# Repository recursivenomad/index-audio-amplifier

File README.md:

🎧 **Tiny USB-C audio amplifier for off-ear BMR speakers**
===========================================================

&nbsp;

> &nbsp;
> ### ***Work in progress***
> &nbsp;

&nbsp;

***Features***
==============

*Coming soon...*

&nbsp;

***How to use***
================

*Coming soon...*

&nbsp;

***License / Access***
======================

This original work is freely available under your choice of the [*MIT-0*](./LICENSE.txt) license or [*CC0-1.0*][URL-CC0] public domain dedication.  
Although attribution is not required, sharing when you've made something with my work is really cool 💖

----------------------

*Repository: <https://gitlab.com/recursivenomad/index-audio-amplifier/>*  
*Contact: <recursivenomad@protonmail.com>*

----------------------

[URL-MIT-0]: <https://opensource.org/license/mit-0/>
[URL-CC0]: <https://creativecommons.org/publicdomain/zero/1.0/>

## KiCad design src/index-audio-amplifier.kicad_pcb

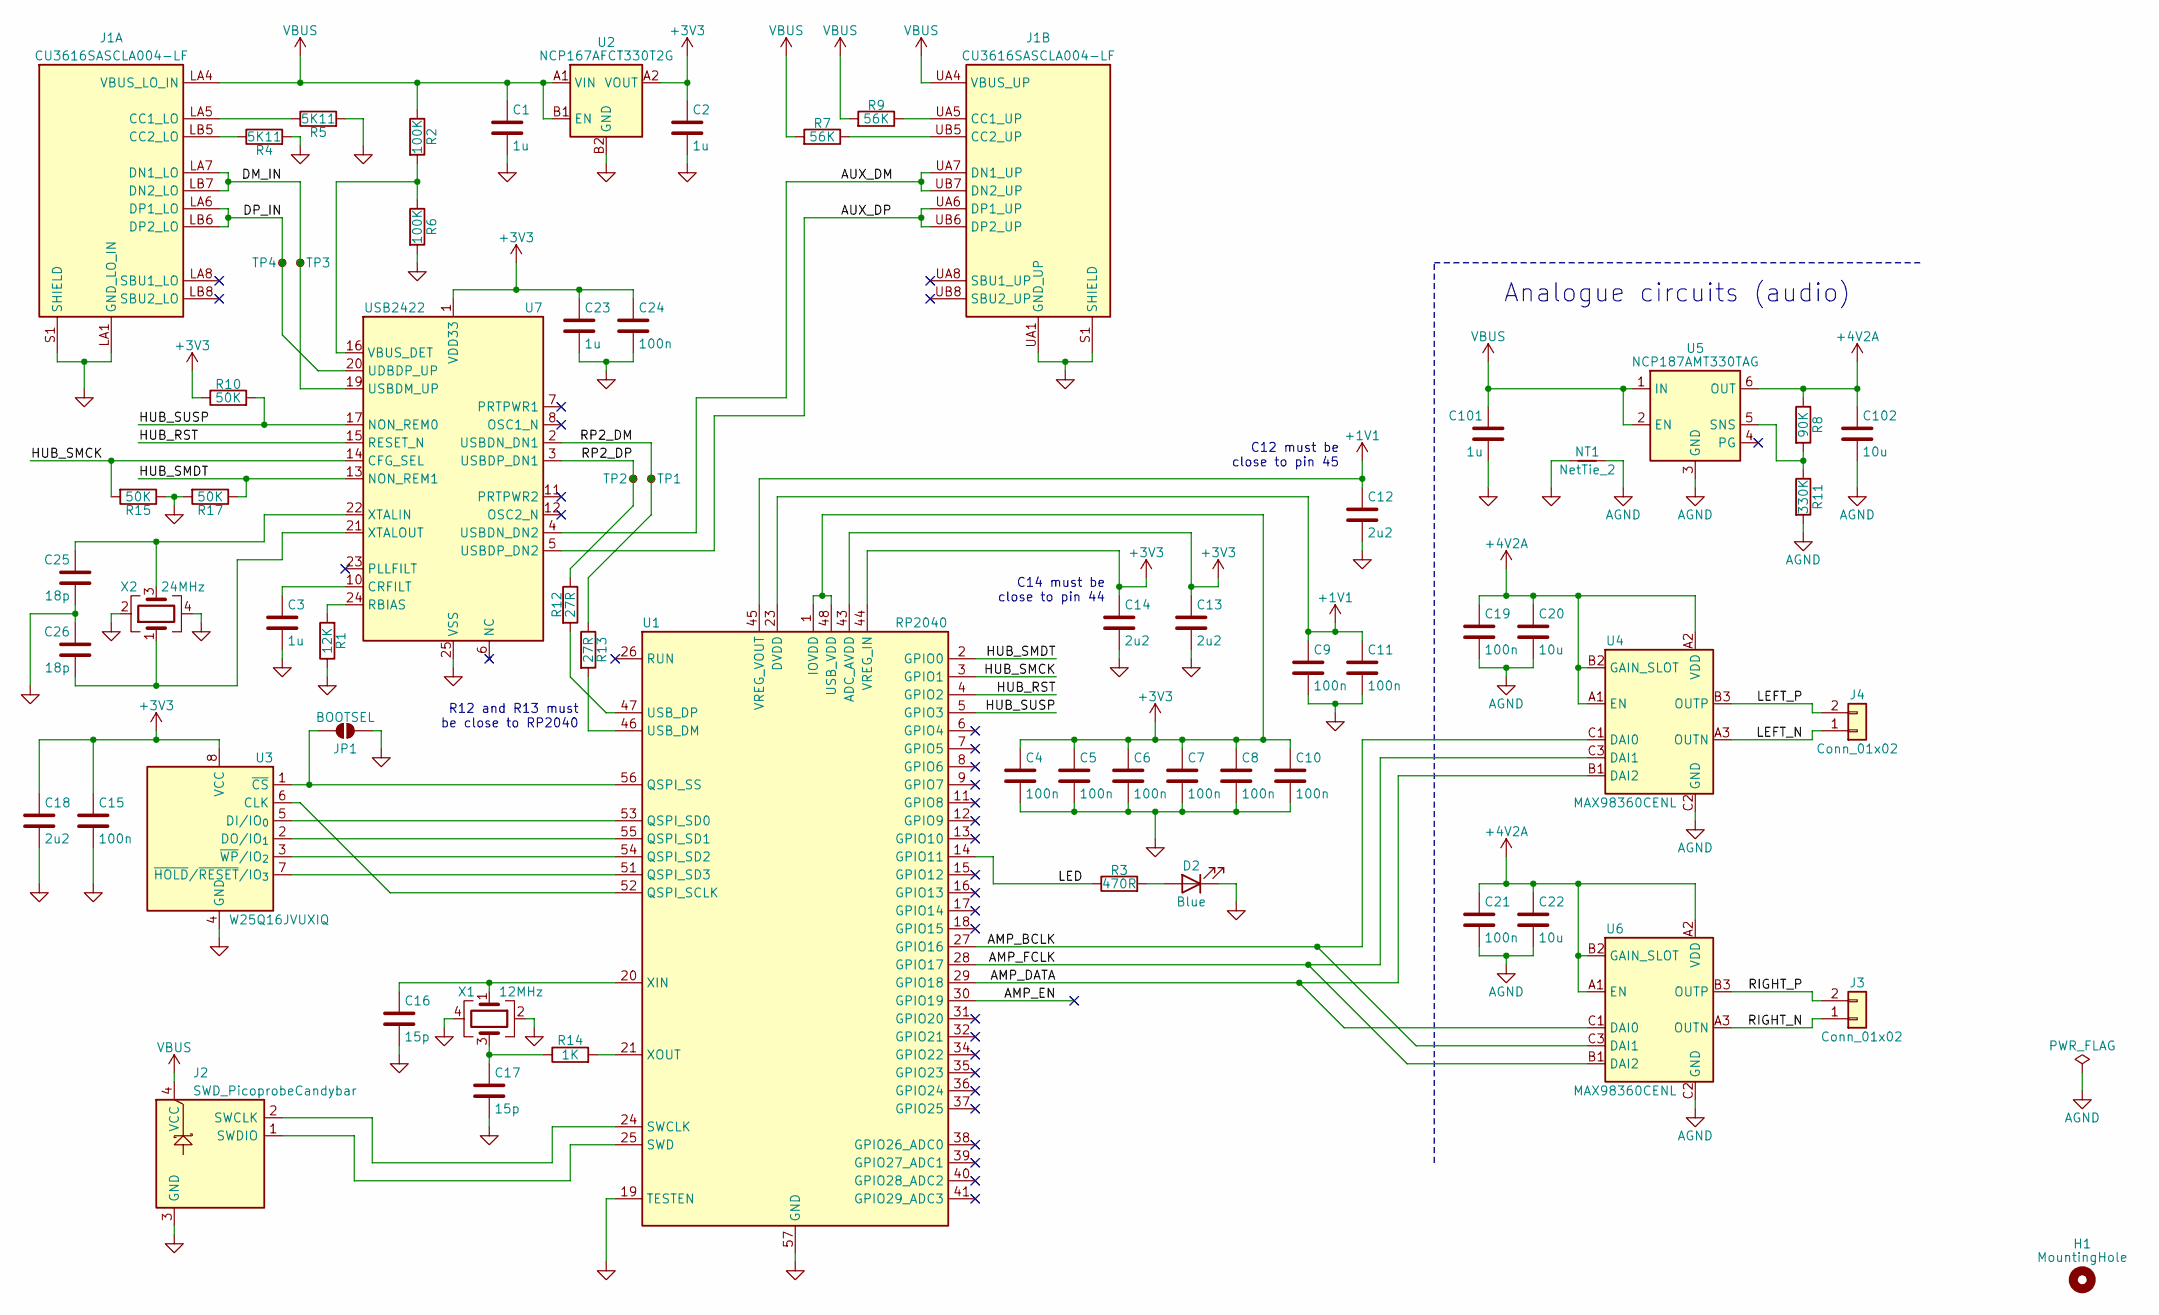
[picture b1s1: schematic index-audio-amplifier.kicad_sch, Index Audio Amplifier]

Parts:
C1, C2, C3, C23, C101: 1u; C_0402_1005Metric
C4, C5, C6, C7, C8, C9, C10, C11, C15, C19, C21, C24: 100n; C_0402_1005Metric
C12, C13, C14: 2u2; C_01005_0402Metric
C16, C17: 15p; C_0402_1005Metric
C18: 2u2; C_0402_1005Metric
C20, C22, C102: 10u; C_0402_1005Metric
C25, C26: 18p; C_0402_1005Metric
D2: Blue; LED_0603_1608Metric
H1: MountingHole; MountingHole_2.2mm_M2_ISO7380
J1: CU3616SASCLA004-LF; USB_C_Receptacle_CviLux_CU36SASCLA004-LF
J2: SWD_PicoprobeCandybar; SWD_PicoprobeCandybar_PressFit_Compact
J3, J4: Conn_01x02; PinHeader_1x02_P1.00mm_Vertical
JP1: BOOTSEL; SolderJumper-2_P1.0mm_Open_RoundedPad0.5x1.0mm
NT1: NetTie_2; NetTie-2_SMD_Pad0.5mm
R1: 12K; R_0402_1005Metric
R2, R6: 100K; R_0402_1005Metric
R3: 470R; R_0402_1005Metric
R4, R5: 5K11; R_0402_1005Metric
R7, R9: 56K; R_0402_1005Metric
R8: 90K; R_0402_1005Metric
R10, R15, R17: 50K; R_0402_1005Metric
R11: 330K; R_0402_1005Metric
R12, R13: 27R; R_0402_1005Metric
R14: 1K; R_0402_1005Metric
TP1, TP2, TP3, TP4: TestPoint_Small; TestPoint_Pad_D0.5mm
U1: RP2040; QFN-56-1EP_7x7mm_P0.4mm_EP3.2x3.2mm
U2: NCP167AFCT330T2G; WLCSP-4_0.64x0.64mm_Layout2x2_P0.35mm
U3: W25Q16JVUXIQ; Winbond_USON-8-1EP_3x2mm_P0.5mm_EP0.2x1.6mm
U4, U6: MAX98360CENL; WLP-9_1.347x1.347mm_Layout3x3_P0.4mm
U5: NCP187AMT330TAG; DFN-6-1EP_2x2mm_P0.65mm_EP1.01x1.7mm
U7: USB2422; VQFN-24-1EP_4x4mm_P0.5mm_EP2.5x2.5mm_ThermalVias
X1: 12MHz; Crystal_SMD_3225-4Pin_3.2x2.5mm
X2: 24MHz; Crystal_SMD_3225-4Pin_3.2x2.5mm

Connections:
+1V1: C9.1, C11.1, C12.1, U1.23 (DVDD), U1.45 (VREG_VOUT), U1.50 (DVDD)
+3V3: C2.1, C4.1, C5.1, C6.1, C7.1, C8.1, C10.1, C13.1, C14.1, C15.1, C18.1, C23.1, C24.1, R10.1, U1.1 (IOVDD), U1.10 (IOVDD), U1.22 (IOVDD), U1.33 (IOVDD), U1.42 (IOVDD), U1.43 (ADC_AVDD), U1.44 (VREG_IN), U1.48 (USB_VDD), U1.49 (IOVDD), U2.A2 (VOUT), U3.8 (VCC), U7.1 (VDD33), U7.9 (VDD33), U7.18 (VDD33)
+4V2A: C19.1, C20.1, C21.1, C22.1, C102.1, R8.1, U4.A1 (EN), U4.A2 (VDD), U4.B2 (GAIN_SLOT), U5.6 (OUT), U6.A1 (EN), U6.A2 (VDD), U6.B2 (GAIN_SLOT)
/AMP_BCLK: U1.27 (GPIO16), U4.C1 (DAI0), U6.C3 (DAI1)
/AMP_DATA: U1.29 (GPIO18), U4.B1 (DAI2), U6.C1 (DAI0)
/AMP_EN: U1.30 (GPIO19)
/AMP_FCLK: U1.28 (GPIO17), U4.C3 (DAI1), U6.B1 (DAI2)
/AUX_DM: J1.UA7 (DN1_UP), J1.UB7 (DN2_UP), U7.4 (USBDN_DN2)
/AUX_DP: J1.UA6 (DP1_UP), J1.UB6 (DP2_UP), U7.5 (USBDP_DN2)
/DM_IN: J1.LA7 (DN1_LO), J1.LB7 (DN2_LO), TP3.1, U7.19 (USBDM_UP)
/DP_IN: J1.LA6 (DP1_LO), J1.LB6 (DP2_LO), TP4.1, U7.20 (UDBDP_UP)
/HUB_RST: U1.4 (GPIO2), U7.15 (RESET_N)
/HUB_SMCK: R15.2, U1.3 (GPIO1), U7.14 (CFG_SEL)
/HUB_SMDT: R17.1, U1.2 (GPIO0), U7.13 (NON_REM1)
/HUB_SUSP: R10.2, U1.5 (GPIO3), U7.17 (NON_REM0)
/LED: R3.1, U1.14 (GPIO11)
/LEFT_N: J4.1, U4.A3 (OUTN)
/LEFT_P: J4.2, U4.B3 (OUTP)
/RIGHT_N: J3.1, U6.A3 (OUTN)
/RIGHT_P: J3.2, U6.B3 (OUTP)
/RP2_DM: R13.1, TP1.1, U7.2 (USBDN_DN1)
/RP2_DP: R12.1, TP2.1, U7.3 (USBDP_DN1)
AGND: C19.2, C20.2, C21.2, C22.2, C102.2, NT1.2, R11.2, U4.C2 (GND), U5.3 (GND), U5.7 (GND), U6.C2 (GND)
GND: C1.2, C2.2, C3.2, C4.2, C5.2, C6.2, C7.2, C8.2, C9.2, C10.2, C11.2, C12.2, C13.2, C14.2, C15.2, C16.2, C17.2, C18.2, C23.2, C24.2, C25.2, C26.1, C101.2, D2.1 (K), J1.LA1 (GND_LO_IN), J1.LA12 (GND_LO), J1.LB1 (GND_LO), J1.LB12 (GND_LO), J1.S1 (SHIELD), J1.UA1 (GND_UP), J1.UA12 (GND_UP), J1.UB1 (GND_UP), J1.UB12 (GND_UP), J2.3 (GND), JP1.2 (B), NT1.1, R1.1, R4.2, R5.2, R6.2, R15.1, R17.2, U1.19 (TESTEN), U1.57 (GND), U2.B2 (GND), U3.4 (GND), U7.25 (VSS), X1.2, X1.4, X2.2, X2.4
unnamed: C17.1, R14.1, X1.3
unnamed: D2.2 (A), R3.2
unnamed: J1.LA5 (CC1_LO), R5.1
unnamed: J1.LB5 (CC2_LO), R4.1
unnamed: J1.UA5 (CC1_UP), R9.1
unnamed: J1.UB5 (CC2_UP), R7.1
unnamed: J2.2 (SWCLK), U1.24 (SWCLK)
unnamed: J2.1 (SWDIO), U1.25 (SWD)
unnamed: JP1.1 (A), U1.56 (QSPI_SS), U3.1 (~CS)
unnamed: U1.52 (QSPI_SCLK), U3.6 (CLK)
unnamed: U1.53 (QSPI_SD0), U3.5 (DI/IO_{0})
unnamed: U1.55 (QSPI_SD1), U3.2 (DO/IO_{1})
unnamed: U1.54 (QSPI_SD2), U3.3 (~WP/IO_{2})
unnamed: U1.51 (QSPI_SD3), U3.7 (~HOLD/~RESET/IO_{3})
unnamed: R13.2, U1.46 (USB_DM)
unnamed: R12.2, U1.47 (USB_DP)
unnamed: C16.1, U1.20 (XIN), X1.1
unnamed: R14.2, U1.21 (XOUT)
unnamed: R8.2, R11.1, U5.5 (SNS)
unnamed: C3.1, U7.10 (CRFILT)
unnamed: R1.2, U7.24 (RBIAS)
unnamed: R2.2, R6.1, U7.16 (VBUS_DET)
unnamed: C25.1, U7.22 (XTALIN), X2.3
unnamed: C26.2, U7.21 (XTALOUT), X2.1
VBUS: C1.1, C101.1, J1.LA4 (VBUS_LO_IN), J1.LA9 (VBUS_LO), J1.LB4 (VBUS_LO), J1.LB9 (VBUS_LO), J1.UA4 (VBUS_UP), J1.UA9 (VBUS_UP), J1.UB4 (VBUS_UP), J1.UB9 (VBUS_UP), J2.4 (VCC), R2.1, R7.2, R9.2, U2.A1 (VIN), U2.B1 (EN), U5.1 (IN), U5.2 (EN)

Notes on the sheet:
C14 must be close to pin 44
R12 and R13 must be close to RP2040
C12 must be close to pin 45
Analogue circuits (audio)

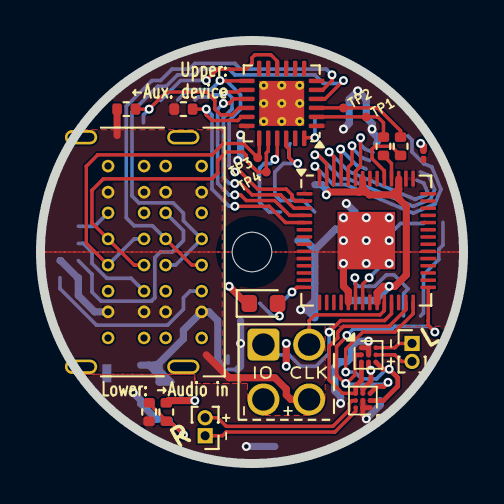
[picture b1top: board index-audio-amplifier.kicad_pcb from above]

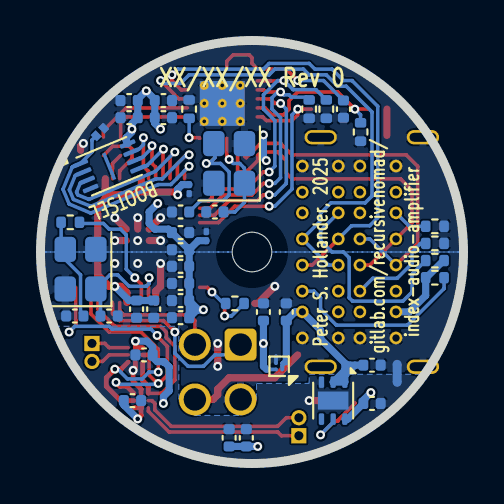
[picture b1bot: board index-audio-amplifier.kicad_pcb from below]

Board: 2 copper layers, 23.5 x 23.5 mm, 65 parts (45 on the bottom side), 48 nets.

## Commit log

2025-08-12 Initialize project
    KiCad 9.0.3
2025-08-12 Initialize project files
    KiCad 9.0.3
2025-08-12 Add & associate `compact-title-block` submodule
2025-08-12 Add & associate debug interface library
2025-08-13 Draw targeted in-situ reference for board layout
    Geometry approximated from Valve Index HMD using calipers
2025-08-13 Create board edge, 0.5mm clearance from nominal
2025-08-13 Recreate Pico schematic (ignoring connectors)
    <https://datasheets.raspberrypi.com/pico/pico-datasheet.pdf#pico-schematic-diagram>
2025-08-13 Add discrete component proximity notes
    Notes adopted from `RP2040_minimal_r2.kicad_pro` in "Minimal-KiCAD.zip"
    from "Hardware design with RP2040":
    <https://datasheets.raspberrypi.com/rp2040/hardware-design-with-rp2040.pdf#minimal-design-example>
2025-08-13 Add PCM5101A for `usb_sound_card` firmware
    Component selection adopted from `pico_vga_sd_aud.pro` in
    "VGA_KiCAD.zip" from "Hardware design with RP2040":
    <https://datasheets.raspberrypi.com/rp2040/hardware-design-with-rp2040.pdf#_the_vga_sd_card_audio_demo_boards_for_raspberry_pi_pico_and_raspberry_pi_pico_w>
    Referenced firmware is on the branch `usb-sound-card` in the
    index-audio-interface repository:
    <https://gitlab.com/recursivenomad/index-audio-interface/-/tree/usb-sound-card/>
2025-08-13 Move I2S pins to match `picoamp` firmware
    Refererenced firmware is on the branch `picoamp-rebase` in the
    index-audio-interface repository:
    <https://gitlab.com/recursivenomad/index-audio-interface/-/tree/picoamp-rebase/>
    Which itself is rebased from sctanf's picoamp `main` branch:
    <https://github.com/sctanf/picoamp/>
2025-08-13 Create MAX98360xEFB symbol
    Component selected by sctanf as described in their picoamp repository
    README:
    <https://github.com/sctanf/picoamp/>
2025-08-13 Add MAX98360xENL (BGA variant)
2025-08-13 Move default text positions
2025-08-13 Replace PCM5101A with 2 MAX98360CENL
    Should be functionally matched to the picoamp firmware now.
    Schematic follows stereo "Typical Application Circuit" from MAX98360x
    datasheet:
    <https://www.analog.com/media/en/technical-documentation/data-sheets/max98360a-max98360d.pdf>
2025-08-13 Remove DNP resistors
2025-08-13 Associate remaining footprints
2025-08-13 Remove unused analogue VSYS monitor (GPIO29)
2025-08-13 Remove external analogue reference
2025-08-13 Add debug interface
2025-08-13 Add screwhead keepout
2025-08-13 Replace Micro-USB with USC-C
2025-08-13 Change audio GND to AGND; add MountingHole
2025-08-14 Add connectors for speaker outputs
2025-08-14 Change MAX98360CENL footprint to custom WLP-9
2025-08-14 Downsize discrete components & swap connectors
2025-08-14 Net tie GND to AGND & isolate analogue circuits
2025-08-14 Initial layout of primarily analogue section
    Removed screwhead keepout in the process; I figure we'll have a high
    enough standoff to avoid any shorts, as we need all the real estate we
    can get!
2025-08-14 Correct RT6150B footprint & reposition schematic
2025-08-14 Consider adding USB hub controller, second port
    Still a major work-in-progress;
    Going to revise heavily after this commit.
2025-08-14 Add CU38 dual stacked USB port multi-unit symbol
    <https://www.cvilux.com/uploads/drawings/101/757/CU36S04S.pdf>
2025-08-14 Replace singular USB ports with dual stacked port
2025-08-15 Add USB2422 Hub Controller symbol
2025-08-15 Fix pins to play nice on mutli-unit symbol
2025-08-15 Add alternate pin definitions to USB2422
2025-08-15 Reposition pins for simpler schematic layout
2025-08-15 Add USB hub controller & dual stacked USB-C port
    Now we can have a port to plug in our audio source, and an auxilliary
    port for plugging in an additional device (such as a face tracker)!
    The setup around USB2422 should ensure it initializes appropriately,
    even when the RP2040 isn't set up to communicate with the USB2422,
    with `*_DN1` being non-removable, and `*_DN2` being removable.
    This will allow for firmware like sctanf's picoamp to be fully drop-in
2025-08-15 Remove NC pins from dual USB C port symbol
    They aren't included in the footprint
2025-08-15 Add & associate dual stack USB-C port footprint
    Uses placeholder Frankenstein model
2025-08-15 Rescale placeholder model
2025-08-15 Adjust thermal spoke orientation
2025-08-15 Add back mounting hole & more net labels
2025-08-15 Update USB2422 footprint to use thermal vias
    Per VSS pin description in datasheet:
    <https://ww1.microchip.com/downloads/aemDocuments/documents/OTH/ProductDocuments/DataSheets/00001726B.pdf#G4.1051294>
2025-08-16 Begin design refactor w/ dual stack USB-C port...
    Gonna keep changing dramatically as I settle in on a design approach,
    but wanted to save some layout here as a "checkpoint" to possibly refer
    back to.
2025-08-16 Move USB2422 controls to GPIO0-3 to assist layout
2025-08-16 Continue refactoring very compact layout
    Feeling pretty good about this second attempt so far...
    Next up: analogue and power regulation
2025-08-16 Tie MAX98360 ENs to VDD to save on traces
2025-08-16 Remove VBUS diode to save space (be careful!)
2025-08-16 Move LED to GPIO14 to support layout
    (also make LED blue)
2025-08-17 Replace all power ICs with NCP167
    Buck/boost as featured on the Raspberry Pi (from which this schematic
    was first based upon) is not needed in this application; voltage will
    always be 5V from VBUS.
    Opted for NCP167 because of its great PSRR, and its cousin NCP1117-3.3
    was mentioned in "Hardware Design with RP2040":
    <https://datasheets.raspberrypi.com/rp2040/hardware-design-with-rp2040.pdf#_input_supply>
2025-08-17 Add tiny solder jumper footprint
2025-08-17 Complete initial PCB layout :)
    Remaining DRC errors/warnings should seemingly be "fine"
    The analogue layout (arguably the most important part) was very cramped
    at the end. If refactoring, consider prioritizing analogue as well as
    decoupling capacitor layout first next time.
    But - feels good to have condensed everything into this tiny footprint!!
2025-08-17 Resolve ERC warning; Rectify BOOTSEL jumper label
    Remaining ERC error/warning are valid, but acceptable. Just be careful.
2025-08-17 Reposition origin & rotate Index reference drawing
2025-08-17 Give capacitors a tad more space under USB port
2025-08-17 Mildly improve Fab layer text readability
2025-08-17 Add silkscreen text and USB Hub bypass test points
2025-08-17 Rotate debug connector text
2025-08-17 Rotate front text to align with mounting angle
2025-08-18 Update power plane geometry
2025-08-19 Replace NCP167 with NCP187
    NCP187 lets us output 4.2V to our amplifiers with SNS feedback.
    <https://www.onsemi.com/download/data-sheet/pdf/ncp187-d.pdf>
    Per the amplifiers' datasheet, this increased VDD will reduce THD+N.
    <https://www.analog.com/media/en/technical-documentation/data-sheets/max98360a-max98360d.pdf>
    We choose 4.2V output because we can expect a minimum of 4.5V to be
    delivered to the board per the USB 2.0 specification, and the NCP187
2025-08-26 Add keepout around USB-C port standoffs
    Measurements aquired from CviLux's CAD model for the part:
    <https://www.cvilux.com/product?id=123&level=type&text=CU%20Series%20USB%20type%20C%20Connector&product_id=1757>
2025-08-27 Adjust USB-C port courtyard
    Tighten courtyard around non-insertive edges
2025-08-29 Add custom model for CU36 USB-C port
    Source for model can be found in index-audio-adapter repository:
    <https://gitlab.com/recursivenomad/index-audio-adapter/-/tree/main/mechanical/src/index-audio-adapters.FCStd>

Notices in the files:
src/index-audio-amplifier.kicad_pcb:
MIT-0 OR CC0-1.0
